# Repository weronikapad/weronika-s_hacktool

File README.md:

## Weronika's Hacktool

A Raspberry pi Pico based hardware tool that can be plugged in via USB-A or or a connecting wire between raspberry's pi pico and a device that you're connecting it to.

## 3D model on onshape:

https://cad.onshape.com/documents/8ba63a7496dc739681835abf/w/b2486c84e183ee5c75462b5f/e/727d0ff90b4b33300ac8e23b?renderMode=0&uiState=6a1f47a38e48adf890f3cb43

## Specifics
Raspberry pi pico is powered by a LiPo battery, that is charged through USB-A and the voltage that pico receives is controled by the power manager. 
1. specifics to connecting hardware parts
   a) battery:
      - connect it with a male to male wire to a connector pin socket 01x02
   
   b) keyboard (look at connector pins on conn_01x04 from KiCad view), (use female to female wires)
     - Pin1 -> wire -> the pin in the keyboard port that the black wire from the picture goes into
     - Pin2 -> wire -> the pin in the keyboard port that the red wire from the picture goes into
     - Pin3 -> wire -> the pin in the keyboard port that the white wire from the picture goes into
     - Pin4 -> wire -> the pin in the keyboard port that the yellow wire from the picture goes into

    c) screen (use female to female wires)(look at connector pins on conn_01x09 from KiCad view)
      - Pin1 -> wire -> vcc on the screen
      - Pin2 -> wire -> GND on the screen
      - Pin3 -> wire -> CS on the screen
      - Pin4 -> wire -> SDO(MISO) on the screen
      - Pin5 -> wire -> SCK on the screen
      - Pin6 -> wire -> SDI(MOSI) on the screen
      - Pin7 -> wire -> DC on the screen
      - Pin8 -> wire -> LED on the screen

## Features

-Raspberry pi Pico
-SD card port (microSD_HC_Molex_104031-0811)
-USB-A (USB_A_CNCTech_1001-011-01101_Horizontal)
-2000 Ohm resistor
-Power manager (TP4057)
-LCD display 
-Keyboard
-LiPo Battery
-Connectors on PCB for screen, keyboard and battery conection

## PCB 
Designed in KiCad, through pico's USB using REPL, pico can send commands to pluged pc and receive and print output, and through UART it can monitor traffic. Independently it can serve as a calculator or a text editor.

**PCB's front copper layer view in KiCad**

**PCB's back copper layer view in KiCad**

**PCB's 3D model, with exact location of specific connectors**

## Schematic

## detailed description on how to use

1. download firmware for pico, and pc
2. download Thonny
3. works best with an sd card connected
4. before assembling everything in the box:
   - plug raspberry pico via wire to your pc
   - push firmware files onto pico
5. to stop any program at any time press esc
6. in order to use the REPL program, or UART:
   - connect pico to at least the screen, and and keyboard
   a) for REPL:
      - in the terminal type "repl"
      - then type the command that you wish to run in your pluged device
     - pico is programed to always run in administrator mode in your pc's cmd so, in order for the rogram to run as intended you must allow it on your pc
    b) for UART:
      -in the terminal type "uart"
7. to use the hacktool independently:
   - connect the pcb to keyboard, screen, and battery
   - charge the battery via USB-A
   a) to use the text editor:
      - type in the terminal "text" + your filename (it can be already saved on sd card or can be created by this command)
        if the file exists:
          - to edit the file type "edit"
          - to delete type "delete"
          - if you change your mind and you no longer wish to engage with the text editor type "leave"
        if it doesn't:
          - type "create" to create it and open it
          - type "leave" if you don't wish to create
8. if you forgot any of those commands type "help" in the main terminal

## why i build this:
I wanted to understand computers and cybersecurity better, i specifically used REPL as i thought it is one of the most universal hacking abilites of raspberry pi pico, I first decided uppon pico because it was all over my feed on tiktok but as it actually turns out it was the perfect fit for my project

## credits:
image from the magazine page, originally distributed by kylatcarter on pinterest: https://pl.pinterest.com/pin/1135399756078582773/ 
readme structure inspired by notaroomba from github

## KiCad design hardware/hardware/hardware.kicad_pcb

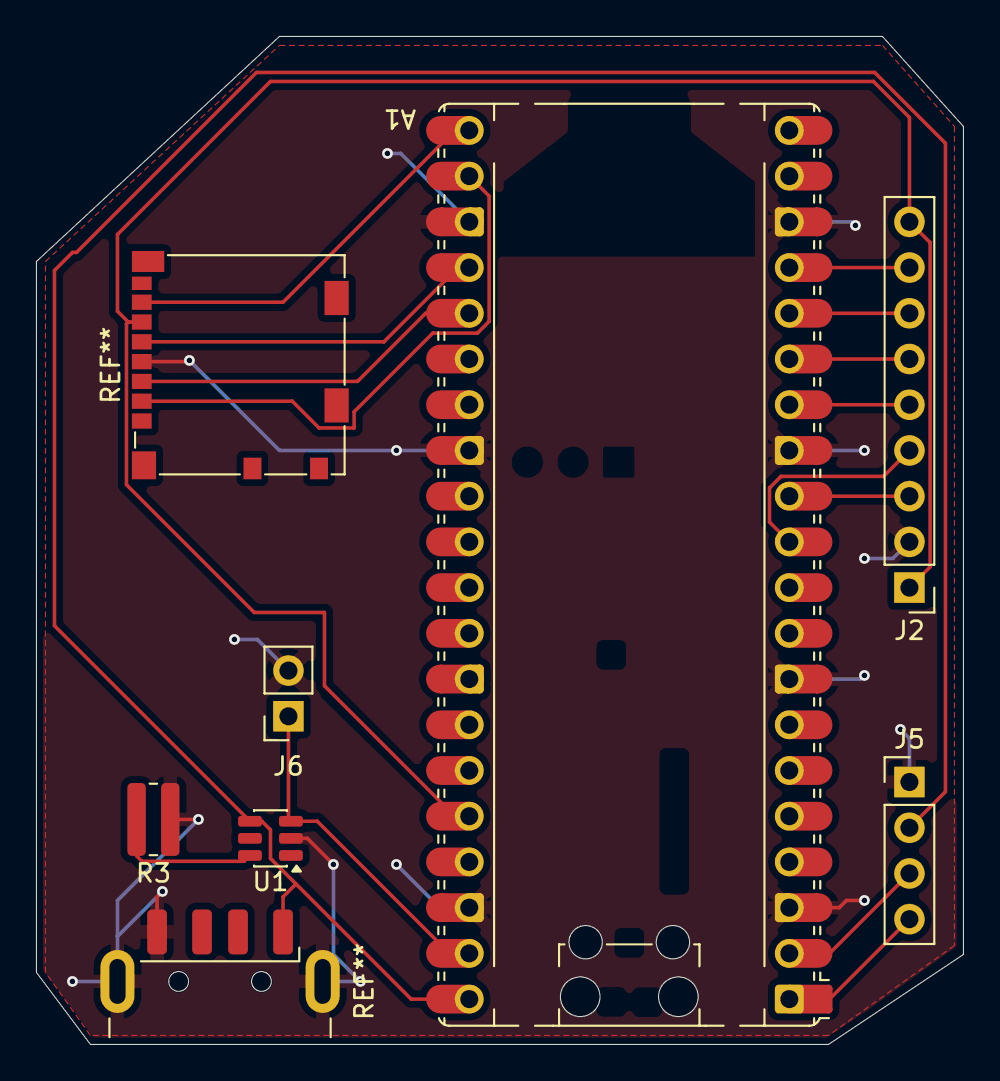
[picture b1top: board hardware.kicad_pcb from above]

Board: 2 copper layers, 51.5 x 56.0 mm, 6 parts (0 on the bottom side), 13 nets.

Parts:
A1: RaspberryPi_Pico; RaspberryPi_Pico_Common_Unspecified
J2: Conn_01x09; PinHeader_1x09_P2.54mm_Vertical
J5: Conn_01x04_Pin; PinHeader_1x04_P2.54mm_Vertical
J6: Conn_01x02; PinSocket_1x02_P2.54mm_Vertical
R3: 2000Ohm; R_0815_2038Metric
U1: TP4057; TSOT-23-6

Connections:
+3.3V: A1.36 (3V3), J2.1, J2.9
GND: A1.3 (GND), A1.8 (GND), A1.13 (GND), A1.18 (GND), A1.23 (GND), A1.28 (GND), A1.38 (GND), J2.2, J5.1, J6.2, R3.1, U1.2 (GND)
unnamed: A1.1 (GPIO0), J5.4
unnamed: A1.2 (GPIO1), J5.3
unnamed: A1.11 (GPIO8), J2.4
unnamed: A1.12 (GPIO9), J2.3
unnamed: A1.14 (GPIO10), J2.5
unnamed: A1.15 (GPIO11), J2.6
unnamed: A1.16 (GPIO12), J2.7
unnamed: A1.17 (GPIO13), J2.8
unnamed: A1.40 (VBUS), J5.2, U1.4 (V_{CC})
unnamed: A1.39 (VSYS), J6.1, U1.3 (BAT)
unnamed: R3.2, U1.6 (PROG)

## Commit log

2026-06-01 firmware
2026-06-01 rest of my files
2026-06-01 readme
2026-06-02 test images
2026-06-02 readmeeeee
2026-06-02 xd
    Corrected typos in wiring instructions and updated images.
2026-06-02 imagesv2
2026-06-02 Fix2
2026-06-02 Fix3
2026-06-02 hdsg
2026-06-02 iuiu
2026-06-02 credits
    Added credit for image source in README.
2026-06-03 ahhhhhhhhh
    Correct formatting for battery connection instructions.
2026-06-03 image
2026-06-03 currency
2026-06-03 clear zine
2026-06-03 render
2026-06-03 grammar
2026-06-05 cfew
2026-06-09 name age and location
2026-06-09 name location age
2026-06-09 zine
    Updated image reference in README and fixed a typo.
